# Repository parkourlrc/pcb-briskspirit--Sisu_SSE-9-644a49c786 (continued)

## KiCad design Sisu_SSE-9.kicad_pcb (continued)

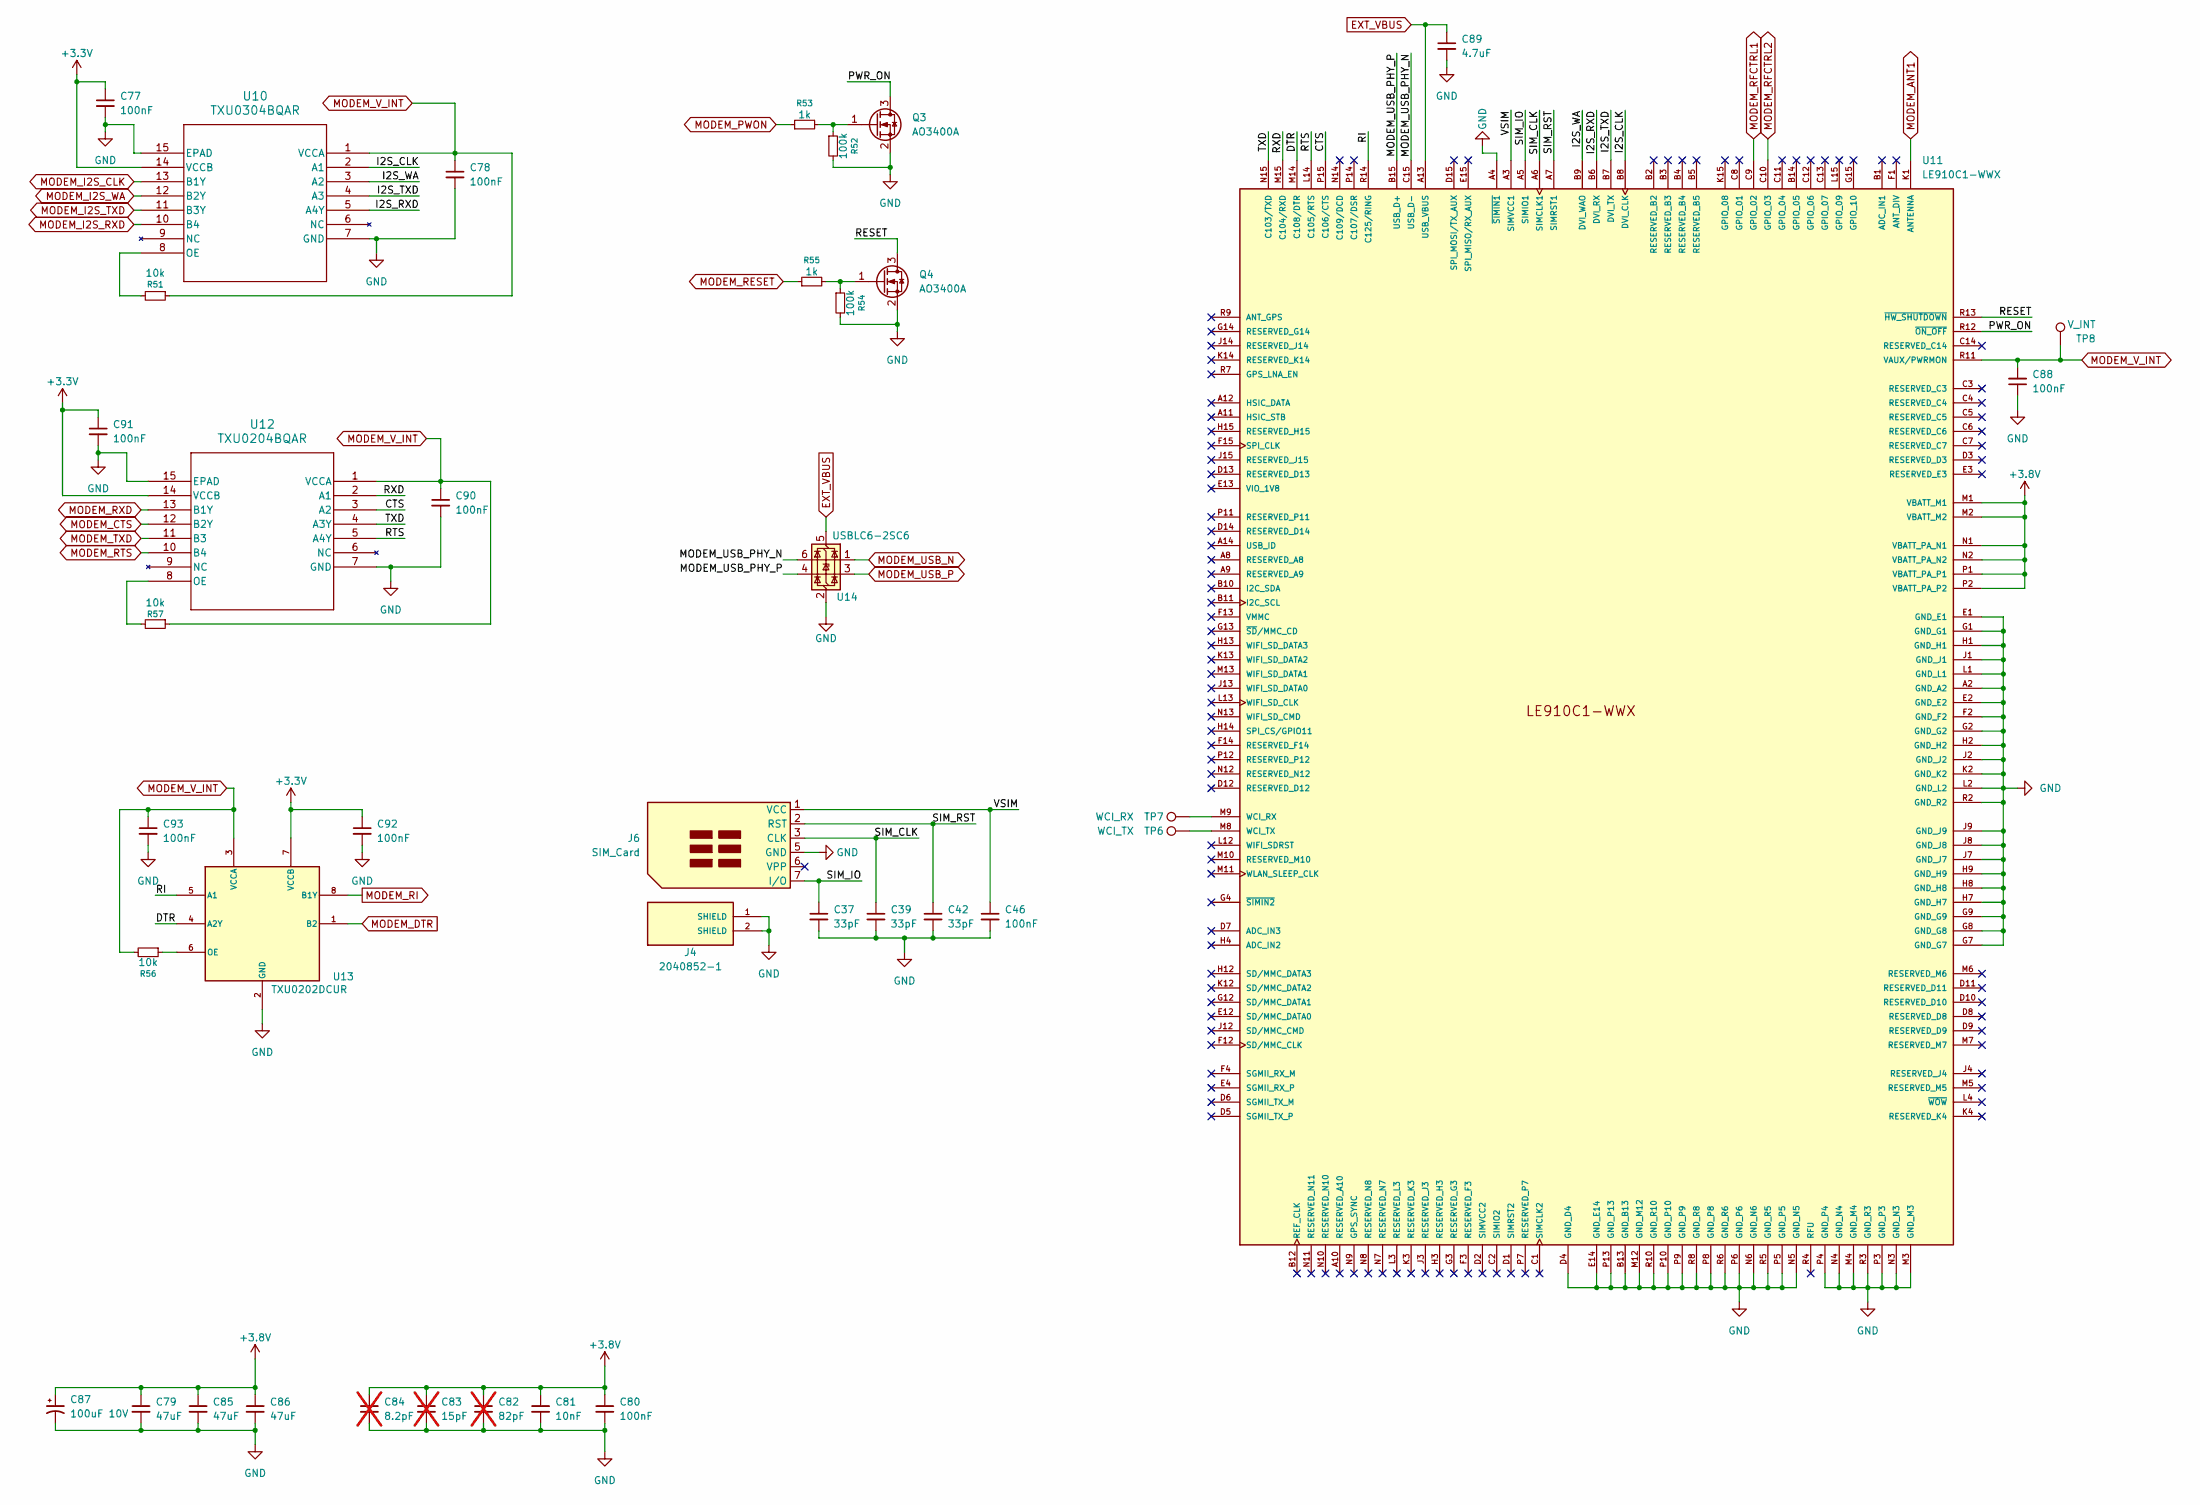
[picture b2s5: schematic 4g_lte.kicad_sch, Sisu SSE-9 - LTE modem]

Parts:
C37, C39, C42: 33pF; C_0402_1005Metric
C46, C77, C78, C80, C88, C90, C91, C92, C93: 100nF; C_0402_1005Metric
C79, C85, C86: 47uF; C_0805_2012Metric
C81: 10nF; C_0402_1005Metric
C82: 82pF; C_0402_1005Metric; not fitted
C83: 15pF; C_0402_1005Metric; not fitted
C84: 8.2pF; C_0402_1005Metric; not fitted
C87: 100uF 10V; CP_EIA-3528-21_Kemet-B
C89: 4.7uF; C_0603_1608Metric
J4: 2040852-1; TE_2040852-1; PARTREV A1
J6: SIM_Card; SIMslot_MUP_C7026-21
Q3, Q4: AO3400A; SOT-23
R51, R56, R57: 10k; R_0402_1005Metric
R52, R54: 100k; R_0402_1005Metric
R53, R55: 1k; R_0402_1005Metric
TP6: WCI_TX; TestPoint_Pad_D1.0mm
TP7: WCI_RX; TestPoint_Pad_D1.0mm
TP8: V_INT; TestPoint_Pad_D1.0mm
U10: TXU0304BQAR; DHWQFN-14-1EP_2.5x3mm_P0.5mm_EP1x1.5mm
U11: LE910C1-WWX; Telit_LE910C1-WWX_LGA-181_29.4x29.4mm; PARTREV 34
U12: TXU0204BQAR; DHWQFN-14-1EP_2.5x3mm_P0.5mm_EP1x1.5mm
U13: TXU0202DCUR; Texas_DCU0008A_VSSOP-8_2.3x2mm_P0.5mm
U14: USBLC6-2SC6; SOT-23-6

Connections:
+3.3V: C77.1, C91.1, C92.1, U10.14 (VCCB), U12.14 (VCCB), U13.7 (VCCB); also elsewhere on the board
+3.8V: C79.1, C80.1, C81.1, C82.1, C83.1, C84.1, C85.1, C86.1, C87.1, U11.M1 (VBATT_M1), U11.M2 (VBATT_M2), U11.N1 (VBATT_PA_N1), U11.N2 (VBATT_PA_N2), U11.P1 (VBATT_PA_P1), U11.P2 (VBATT_PA_P2); also elsewhere on the board
/4G LTE/CTS: U11.P15 (C106/CTS), U12.3 (A2)
/4G LTE/DTR: U11.M14 (C108/DTR), U13.4 (A2Y)
/4G LTE/I2S_CLK: U10.2 (A1), U11.B8 (DVI_CLK)
/4G LTE/I2S_RXD: U10.5 (A4Y), U11.B6 (DVI_RX)
/4G LTE/I2S_TXD: U10.4 (A3), U11.B7 (DVI_TX)
/4G LTE/I2S_WA: U10.3 (A2), U11.B9 (DVI_WAO)
/4G LTE/MODEM_USB_PHY_N: U11.C15 (USB_D-), U14.6 (I/O1)
/4G LTE/MODEM_USB_PHY_P: U11.B15 (USB_D+), U14.4 (I/O2)
/4G LTE/PWR_ON: Q3.3 (D), U11.R12 (~ON_OFF)
/4G LTE/RESET: Q4.3 (D), U11.R13 (~HW_SHUTDOWN)
/4G LTE/RI: U11.R14 (C125/RING), U13.5 (A1)
/4G LTE/RTS: U11.L14 (C105/RTS), U12.5 (A4Y)
/4G LTE/RXD: U11.M15 (C104/RXD), U12.2 (A1)
/4G LTE/SIM_CLK: C39.1, J6.3 (CLK), U11.A6 (SIMCLK1)
/4G LTE/SIM_IO: C37.1, J6.7 (I/O), U11.A5 (SIMIO1)
/4G LTE/SIM_RST: C42.1, J6.2 (RST), U11.A7 (SIMRST1)
/4G LTE/TXD: U11.N15 (C103/TXD), U12.4 (A3Y)
/4G LTE/VSIM: C46.1, J6.1 (VCC), U11.A3 (SIMVCC1)
EXT_VBUS: C89.1, U11.A13 (USB_VBUS), U14.5 (VBUS); also elsewhere on the board
GND: C37.2, C39.2, C42.2, C46.2, C77.2, C78.2, C79.2, C80.2, C81.2, C82.2, C83.2, C84.2, C85.2, C86.2, C87.2, C88.1, C89.2, C90.2, C91.2, C92.2, C93.2, J4.1 (SHIELD), J4.2 (SHIELD), J6.5 (GND), Q3.2 (S), Q4.2 (S), R52.2, R54.2, U10.7 (GND), U10.15 (EPAD), U11.A2 (GND_A2), U11.A4 (~SIMIN1), U11.B13 (GND_B13), U11.D4 (GND_D4), U11.E1 (GND_E1), U11.E2 (GND_E2), U11.E14 (GND_E14), U11.F2 (GND_F2), U11.G1 (GND_G1), U11.G2 (GND_G2), U11.G7 (GND_G7), U11.G8 (GND_G8), U11.G9 (GND_G9), U11.H1 (GND_H1), U11.H2 (GND_H2), U11.H7 (GND_H7), U11.H8 (GND_H8), U11.H9 (GND_H9), U11.J1 (GND_J1), U11.J2 (GND_J2), U11.J7 (GND_J7), U11.J8 (GND_J8), U11.J9 (GND_J9), U11.K2 (GND_K2), U11.L1 (GND_L1), U11.L2 (GND_L2), U11.M3 (GND_M3), U11.M4 (GND_M4), U11.M12 (GND_M12), U11.N3 (GND_N3), U11.N4 (GND_N4), U11.N5 (GND_N5), U11.N6 (GND_N6), U11.P3 (GND_P3), U11.P4 (GND_P4), U11.P5 (GND_P5), U11.P6 (GND_P6), U11.P8 (GND_P8), U11.P9 (GND_P9), U11.P10 (GND_P10), U11.P13 (GND_P13), U11.R2 (GND_R2), U11.R3 (GND_R3), U11.R5 (GND_R5), U11.R6 (GND_R6), U11.R8 (GND_R8), U11.R10 (GND_R10), U12.7 (GND), U12.15 (EPAD), U13.2 (GND), U14.2 (GND); also elsewhere on the board
MODEM_ANT1: U11.K1 (ANTENNA); also elsewhere on the board
MODEM_CTS: U12.12 (B2Y); also elsewhere on the board
MODEM_DTR: U13.1 (B2); also elsewhere on the board
MODEM_I2S_CLK: U10.13 (B1Y); also elsewhere on the board
MODEM_I2S_RXD: U10.10 (B4); also elsewhere on the board
MODEM_I2S_TXD: U10.11 (B3Y); also elsewhere on the board
MODEM_I2S_WA: U10.12 (B2Y); also elsewhere on the board
MODEM_PWON: R53.1; also elsewhere on the board
MODEM_RESET: R55.1; also elsewhere on the board
MODEM_RFCTRL1: U11.C9 (GPIO_02); also elsewhere on the board
MODEM_RFCTRL2: U11.C10 (GPIO_03); also elsewhere on the board
MODEM_RI: U13.8 (B1Y); also elsewhere on the board
MODEM_RTS: U12.10 (B4); also elsewhere on the board
MODEM_RXD: U12.13 (B1Y); also elsewhere on the board
MODEM_TXD: U12.11 (B3); also elsewhere on the board
MODEM_USB_N: U14.1 (I/O1); also elsewhere on the board
MODEM_USB_P: U14.3 (I/O2); also elsewhere on the board
MODEM_V_INT: C78.1, C88.2, C90.1, C93.1, R51.1, R56.2, R57.1, TP8.1 (1_1), U10.1 (VCCA), U11.R11 (VAUX/PWRMON), U12.1 (VCCA), U13.3 (VCCA); also elsewhere on the board
unnamed: Q3.1 (G), R52.1, R53.2
unnamed: Q4.1 (G), R54.1, R55.2
unnamed: R51.2, U10.8 (OE)
unnamed: TP7.1 (1_1), U11.M9 (WCI_RX)
unnamed: TP6.1 (1_1), U11.M8 (WCI_TX)
unnamed: R57.2, U12.8 (OE)
unnamed: R56.1, U13.6 (OE)

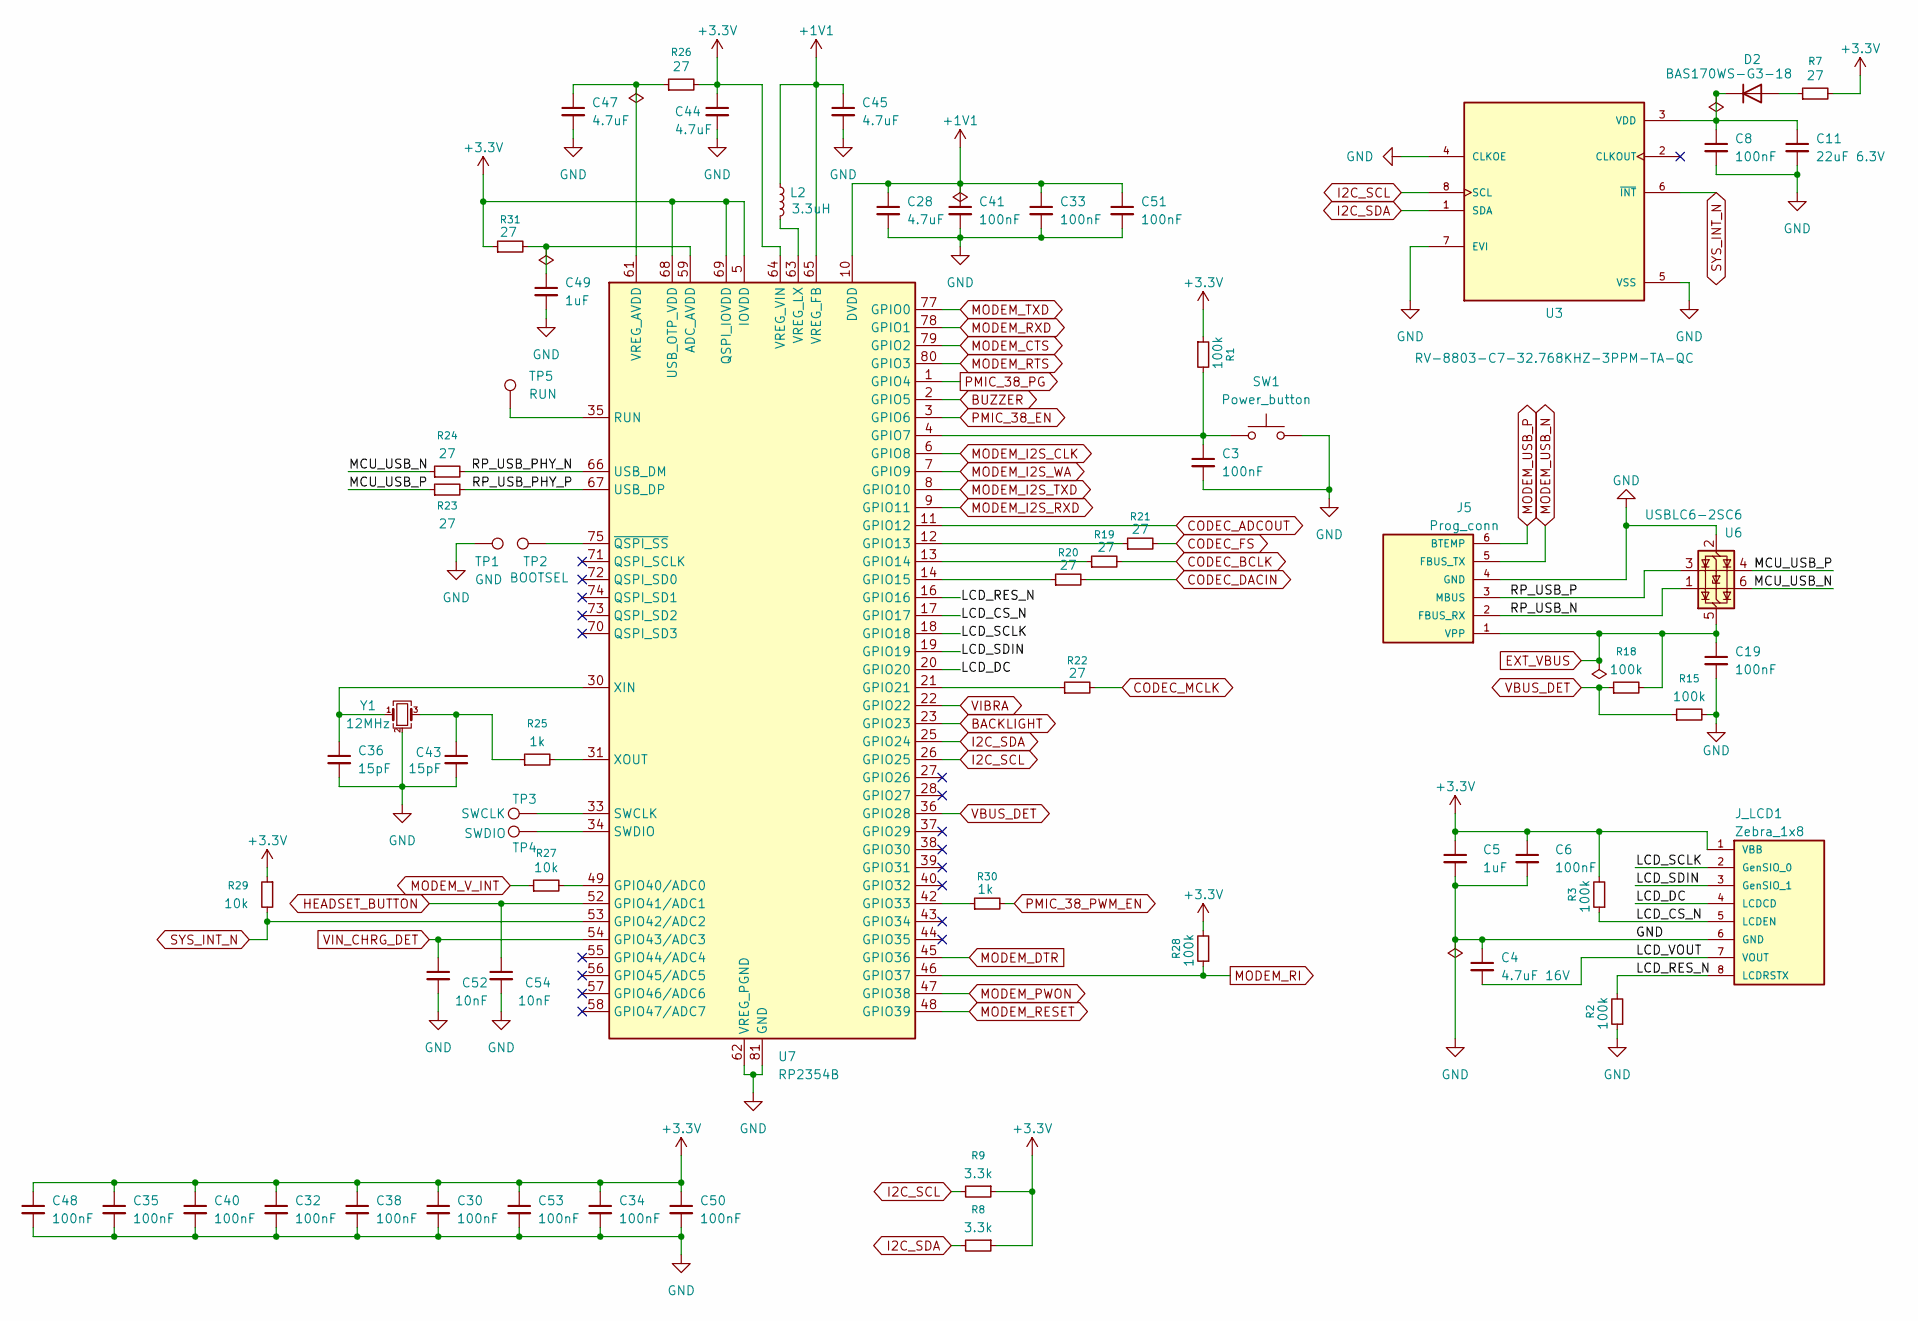
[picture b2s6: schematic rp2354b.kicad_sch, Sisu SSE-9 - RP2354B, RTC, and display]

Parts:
C3, C6, C8, C19, C30, C32, C33, C34, C35, C38, C40, C41, C48, C50, C51, C53: 100nF; C_0402_1005Metric
C4: 4.7uF 16V; C_0603_1608Metric
C5, C49: 1uF; C_0402_1005Metric
C11: 22uF 6.3V; C_0603_1608Metric
C28, C44, C45, C47: 4.7uF; C_0603_1608Metric
C36, C43: 15pF; C_0402_1005Metric
C52, C54: 10nF; C_0402_1005Metric
D2: BAS170WS-G3-18; D_SOD-323
J5: Prog_conn; 3210_prog_connector
J_LCD1: Zebra_1x8; 3210_display_zebra
L2: 3.3uH; L_Changjiang_FTC201610S; MPN AOTA-B201610S3R3-101-T
R1, R2, R3, R15, R18, R28: 100k; R_0402_1005Metric
R7, R19, R20, R21, R22, R23, R24, R26, R31: 27; R_0402_1005Metric
R8, R9: 3.3k; R_0402_1005Metric
R25, R30: 1k; R_0402_1005Metric
R27, R29: 10k; R_0402_1005Metric
SW1: Power_button; Panasonic_EVQPUJ_EVQPUA
TP1: GND; TestPoint_Pad_D1.0mm
TP2: BOOTSEL; TestPoint_Pad_D1.0mm
TP3: SWCLK; TestPoint_Pad_D1.0mm
TP4: SWDIO; TestPoint_Pad_D1.0mm
TP5: RUN; TestPoint_Pad_D1.0mm
U3: RV-8803-C7-32.768KHZ-3PPM-TA-QC; IC_RV-8803-C7-32.768KHZ-3PPM-TA-QC; PARTREV 5.1/06.2018
U6: USBLC6-2SC6; SOT-23-6
U7: RP2354B; RP2354B_QFN-80-1EP_10x10mm_P0.4mm_EP3.4x3.4mm
Y1: 12MHz; Crystal_SMD_3225-4Pin_3.2x2.5mm

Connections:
+1V1: C28.1, C33.1, C41.1, C45.1, C51.1, L2.1, U7.10 (DVDD), U7.32 (DVDD), U7.51 (DVDD), U7.65 (VREG_FB)
+3.3V: C5.1, C6.1, C30.1, C32.1, C34.1, C35.1, C38.1, C40.1, C44.1, C48.1, C50.1, C53.1, J_LCD1.1 (VBB), R1.1, R3.2, R7.2, R8.1, R9.1, R26.2, R28.2, R29.1, R31.1, U7.5 (IOVDD), U7.15 (IOVDD), U7.24 (IOVDD), U7.29 (IOVDD), U7.41 (IOVDD), U7.50 (IOVDD), U7.60 (IOVDD), U7.64 (VREG_VIN), U7.68 (USB_OTP_VDD), U7.69 (QSPI_IOVDD), U7.76 (IOVDD); also elsewhere on the board
/RP2354B / RTC / DISPLAY/LCD_CS_N: J_LCD1.5 (LCDEN), R3.1, U7.17 (GPIO17)
/RP2354B / RTC / DISPLAY/LCD_DC: J_LCD1.4 (LCDCD), U7.20 (GPIO20)
/RP2354B / RTC / DISPLAY/LCD_RES_N: J_LCD1.8 (LCDRSTX), R2.2, U7.16 (GPIO16)
/RP2354B / RTC / DISPLAY/LCD_SCLK: J_LCD1.2 (GenSIO_0), U7.18 (GPIO18)
/RP2354B / RTC / DISPLAY/LCD_SDIN: J_LCD1.3 (GenSIO_1), U7.19 (GPIO19)
/RP2354B / RTC / DISPLAY/LCD_VOUT: C4.2, J_LCD1.7 (VOUT)
/RP2354B / RTC / DISPLAY/MCU_USB_N: R24.1, U6.6 (I/O1)
/RP2354B / RTC / DISPLAY/MCU_USB_P: R23.1, U6.4 (I/O2)
/RP2354B / RTC / DISPLAY/RP_USB_N: J5.2 (FBUS_RX), U6.1 (I/O1)
/RP2354B / RTC / DISPLAY/RP_USB_P: J5.3 (MBUS), U6.3 (I/O2)
/RP2354B / RTC / DISPLAY/RP_USB_PHY_N: R24.2, U7.66 (USB_DM)
/RP2354B / RTC / DISPLAY/RP_USB_PHY_P: R23.2, U7.67 (USB_DP)
BACKLIGHT: U7.23 (GPIO23); also elsewhere on the board
BUZZER: U7.2 (GPIO5); also elsewhere on the board
CODEC_ADCOUT: U7.11 (GPIO12); also elsewhere on the board
CODEC_BCLK: R19.2; also elsewhere on the board
CODEC_DACIN: R20.2; also elsewhere on the board
CODEC_FS: R21.2; also elsewhere on the board
CODEC_MCLK: R22.2; also elsewhere on the board
EXT_VBUS: C19.1, J5.1 (VPP), R18.2, U6.5 (VBUS); also elsewhere on the board
GND: C3.2, C4.1, C5.2, C6.2, C8.2, C11.2, C19.2, C28.2, C30.2, C32.2, C33.2, C34.2, C35.2, C36.2, C38.2, C40.2, C41.2, C43.2, C44.2, C45.2, C47.2, C48.2, C49.2, C50.2, C51.2, C52.2, C53.2, C54.2, J5.4 (GND), J_LCD1.6 (GND), R2.1, R15.2, SW1.2, TP1.1 (1_1), U3.4 (CLKOE), U3.5 (VSS), U3.7 (EVI), U6.2 (GND), U7.62 (VREG_PGND), U7.81 (GND), Y1.2 (G), Y1.4 (G); also elsewhere on the board
HEADSET_BUTTON: C54.1, U7.52 (GPIO41/ADC1); also elsewhere on the board
I2C_SCL: R9.2, U3.8 (SCL), U7.26 (GPIO25); also elsewhere on the board
I2C_SDA: R8.2, U3.1 (SDA), U7.25 (GPIO24); also elsewhere on the board
MODEM_CTS: U7.79 (GPIO2); also elsewhere on the board
MODEM_DTR: U7.45 (GPIO36); also elsewhere on the board
MODEM_I2S_CLK: U7.6 (GPIO8); also elsewhere on the board
MODEM_I2S_RXD: U7.9 (GPIO11); also elsewhere on the board
MODEM_I2S_TXD: U7.8 (GPIO10); also elsewhere on the board
MODEM_I2S_WA: U7.7 (GPIO9); also elsewhere on the board
MODEM_PWON: U7.47 (GPIO38); also elsewhere on the board
MODEM_RESET: U7.48 (GPIO39); also elsewhere on the board
MODEM_RI: R28.1, U7.46 (GPIO37); also elsewhere on the board
MODEM_RTS: U7.80 (GPIO3); also elsewhere on the board
MODEM_RXD: U7.78 (GPIO1); also elsewhere on the board
MODEM_TXD: U7.77 (GPIO0); also elsewhere on the board
MODEM_USB_N: J5.5 (FBUS_TX); also elsewhere on the board
MODEM_USB_P: J5.6 (BTEMP); also elsewhere on the board
MODEM_V_INT: R27.1; also elsewhere on the board
unnamed: C43.1, R25.1, Y1.3
unnamed: D2.2 (A), R7.1
unnamed: C8.1, C11.1, D2.1 (K), U3.3 (VDD)
unnamed: C49.1, R31.2, U7.59 (ADC_AVDD)
unnamed: C3.1, R1.2, SW1.1, U7.4 (GPIO7)
unnamed: R21.1, U7.12 (GPIO13)
unnamed: R19.1, U7.13 (GPIO14)
unnamed: R20.1, U7.14 (GPIO15)
unnamed: R22.1, U7.21 (GPIO21)
unnamed: R30.1, U7.42 (GPIO33)
unnamed: R27.2, U7.49 (GPIO40/ADC0)
unnamed: TP5.1 (1_1), U7.35 (RUN)
unnamed: TP3.1 (1_1), U7.33 (SWCLK)
unnamed: TP4.1 (1_1), U7.34 (SWDIO)
unnamed: C47.1, R26.1, U7.61 (VREG_AVDD)
unnamed: L2.2, U7.63 (VREG_LX)
unnamed: C36.1, U7.30 (XIN), Y1.1
unnamed: R25.2, U7.31 (XOUT)
unnamed: TP2.1 (1_1), U7.75 (~QSPI_SS)
PMIC_38_EN: U7.3 (GPIO6); also elsewhere on the board
PMIC_38_PG: U7.1 (GPIO4); also elsewhere on the board
PMIC_38_PWM_EN: R30.2; also elsewhere on the board
SYS_INT_N: R29.2, U3.6 (~INT), U7.53 (GPIO42/ADC2); also elsewhere on the board
VBUS_DET: R15.1, R18.1, U7.36 (GPIO28)
VIBRA: U7.22 (GPIO22); also elsewhere on the board
VIN_CHRG_DET: C52.1, U7.54 (GPIO43/ADC3); also elsewhere on the board

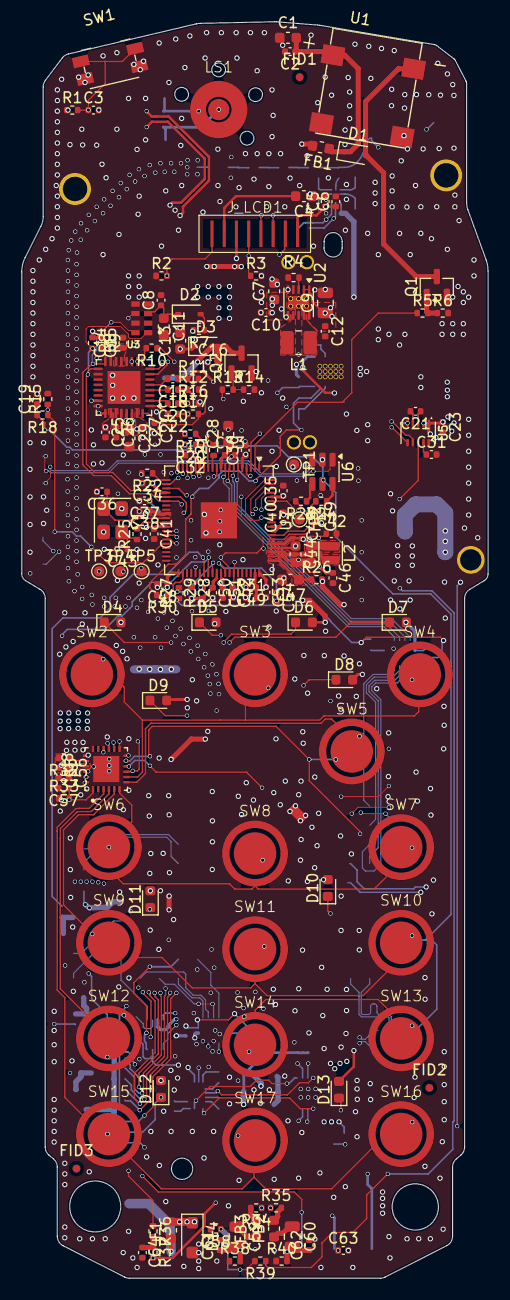
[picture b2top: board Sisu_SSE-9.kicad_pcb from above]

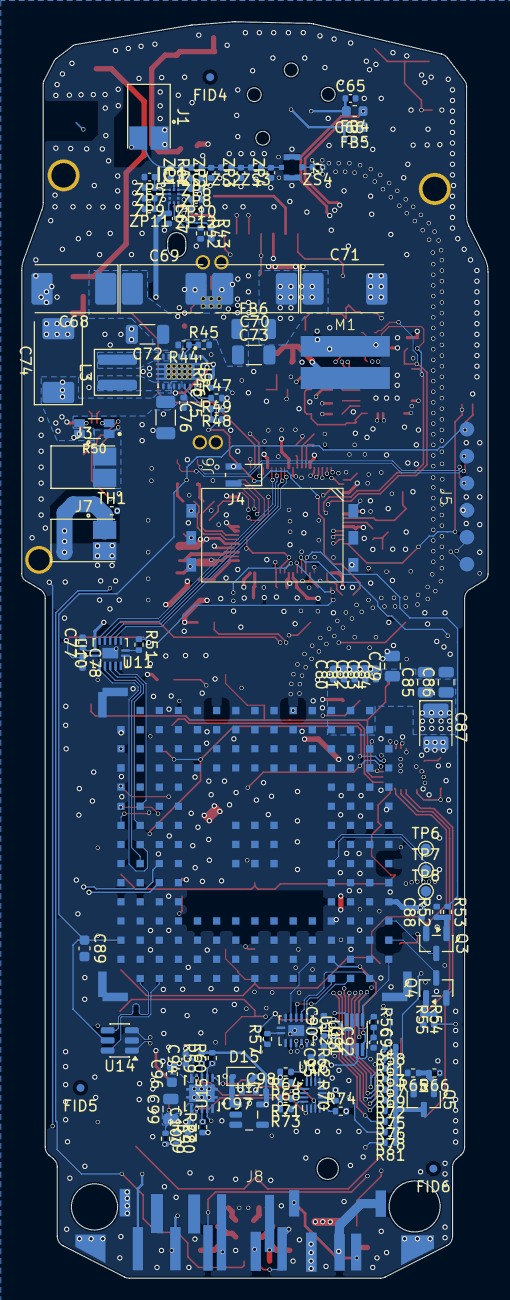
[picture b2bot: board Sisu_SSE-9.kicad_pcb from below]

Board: 6 copper layers, 43.9 x 118.2 mm, 296 parts (127 on the bottom side), 192 nets.

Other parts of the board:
FID1, FID2, FID3, FID4, FID5, FID6: Fiducial_0.75mm_Mask1.5mm
H1, H2: PTH_GND_Hole_2.30mm
H3, H4, H5, H6: PTH_GND_Hole_0.95mm
H7: PTH_GND_Hole_2.00mm

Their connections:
GND: H1.1 (GND), H2.1 (GND), H3.1 (GND), H4.1 (GND), H5.1 (GND), H6.1 (GND), H7.1 (GND); also elsewhere on the board

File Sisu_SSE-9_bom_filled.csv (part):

"Id";"Designator";"Footprint";"Quantity";"Designation";"Supplier and ref";"MPN Source/Reason";"Digi-Key PN";"Preferred Supplier";"Digi-Key/Product URL";"Stock Check";"Footprint Check";"Value/Voltage Check";"Assembly/Review Notes"
"1";"C1, C7, C11, C29, C96";"C_0603_1608Metric";"5";"22uF 6.3V";"GRM188R60J226MEA0J";"current schematic Datasheet/MPN; prior supplier metadata retained";"490-GRM188R60J226MEA0JCT-ND";"Digi-Key";"https://www.digikey.com/en/products/detail/murata-electronic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";"Digi-Key search showed in stock; verify at order time.";"OK: 0603 MLCC.";"OK: 22uF 6.3V. | Selected 22uF 6.3V; verify if rail can exceed 6.3V.";""
"2";"C2, C3, C6, C8, C10, C12, C14, C15, C16, C19, C23, C25, C27, C30, C32, C33, C34, C35, C38, C40, C41, C46, C48, C50, C51, C53, C56, C67, C75, C77, C78, C80, C88, C90, C91, C92, C93, C95, C97, C100";"C_0402_1005Metric";"40";"100nF";"GCM155R71H104KE02J";"current schematic Datasheet/MPN; prior supplier metadata retained";"";"Digi-Key";"https://www.digikey.com/en/products/detail/murata-electronic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";"Digi-Key search showed high stock; verify at order time.";"OK: 0402 MLCC.";"OK: 100nF; 50V X7R family.";""
"3";"C4";"C_0603_1608Metric";"1";"4.7uF 16V";"CL10A475KO8NNNC";"current schematic Datasheet/MPN; prior supplier metadata retained";"";"Digi-Key";"https://www.digikey.com/en/products/detail/samsung-electro-m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";"Digi-Key search showed in stock; verify at order time.";"OK: 0603 MLCC. | OK after replacement: selected MPN is 0603.";"OK: 4.7uF 16V. | OK: 4.7uF; selected 16V part.";""
"4";"C5, C17, C18, C20, C22, C24, C31, C49, C94, C98";"C_0402_1005Metric";"10";"1uF";"CL05A105KO5NNNC";"current schematic Datasheet/MPN; prior supplier metadata retained";"";"Digi-Key";"https://www.digikey.com/en/products/detail/samsung-electro-m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";"Digi-Key search showed high stock; verify at order time.";"OK: 0402 MLCC.";"OK: 1uF; 16V X5R/X7R-class MLCC.";"C98 specifically should be retrofitted from 1uF to 4.7uF for TPS7B69 stability; see ERRATA.md."
"5";"C9";"C_0805_2012Metric";"1";"22uF 10V";"GRM21BR61A226ME51L";"current schematic Datasheet/MPN; prior supplier metadata retained";"";"Digi-Key";"https://www.digikey.com/en/products/detail/murata-electronic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";"Verify at order time.";"OK: 0805 MLCC.";"OK: 22uF 10V.";""
"6";"C13";"C_0603_1608Metric";"1";"22uF";"GRM188R60J226MEA0J";"current schematic Datasheet/MPN; prior supplier metadata retained";"490-GRM188R60J226MEA0JCT-ND";"Digi-Key";"https://www.digikey.com/en/products/detail/murata-electronic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";"Digi-Key search showed in stock; verify at order time.";"OK: 0603 MLCC.";"OK: 22uF 6.3V. | Selected 22uF 6.3V; verify if rail can exceed 6.3V.";""
"7";"C21";"C_0402_1005Metric";"1";"470nF";"GRM155R61A474KE15D";"current schematic Datasheet/MPN; prior supplier metadata retained";"";"";"";"Not rechecked for revB2.";"Current KiCad footprint: C_0402_1005Metric; supplier land pattern not rechecked in this update.";"Current schematic value(s): 470nF; reverify against MPN before ordering.";""
"8";"C26, C55";"C_0402_1005Metric";"2";"4.7uF";"CL05A475MP5NRNC";"current schematic Datasheet/MPN; prior supplier metadata retained";"";"Digi-Key";"https://www.digikey.com/en/products/detail/samsung-electro-m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";"Digi-Key search showed high stock; verify at order time.";"OK: 0402 MLCC.";"OK: 4.7uF; 10V-class MLCC.";""
"9";"C28, C44, C45, C47, C89";"C_0603_1608Metric";"5";"4.7uF";"CL10A475KO8NNNC";"current schematic Datasheet/MPN; prior supplier metadata retained";"";"Digi-Key";"https://www.digikey.com/en/products/detail/samsung-electro-m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";"Digi-Key search showed in stock; verify at order time.";"OK: 0603 MLCC. | OK after replacement: selected MPN is 0603.";"OK: 4.7uF 16V. | OK: 4.7uF; selected 16V part.";""
"10";"C36, C43";"C_0402_1005Metric";"2";"15pF";"GJM1555C1H150FB01D";"current schematic Datasheet/MPN; prior supplier metadata retained";"";"Digi-Key";"https://www.digikey.com/en/products/filter/ceramic-capacitor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";"Digi-Key filter showed 15pF 0402 C0G options in stock; verify exact MPN at order time.";"OK: 0402 C0G.";"OK: 15pF, 50V C0G/NP0; matches Raspberry Pi RP2350-family guidance for ABM8-272-T3 with expected board parasitics. | OK: 15pF, 50V C0G/NP0.";""
"11";"C37, C39, C42, C58, C61, C62, C63, C65, C66";"C_0402_1005Metric";"9";"33pF";"CL05C330JB5NNNC";"current schematic Datasheet/MPN; prior supplier metadata retained";"1276-1272-1-ND";"Digi-Key";"https://www.digikey.com/en/products/detail/samsung-electro-m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";"Digi-Key product page says ships today; verify at order time.";"OK: 0402 C0G.";"OK: 33pF, 50V C0G/NP0.";""
"12";"C52, C54, C57, C81";"C_0402_1005Metric";"4";"10nF";"GCM155R71H103KA55D";"current schematic Datasheet/MPN; prior supplier metadata retained";"490-4762-1-ND";"Digi-Key";"https://www.digikey.com/en/products/detail/murata-electronic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";"Digi-Key showed in stock; verify at order time.";"OK after replacement: selected 0402. Original GRM1885C1H103JA01D is 0603 and does not match PCB.";"OK: 10nF 50V, but selected dielectric is X7R. 10nF C0G generally was not available in 0402 from the in-stock Digi-Key search.";""
"13";"C59, C60";"C_0805_2012Metric";"2";"47uF 6.3V";"CL21A476MQYNNNG";"current schematic Datasheet/MPN; prior supplier metadata retained";"1276-6467-1-ND";"Digi-Key";"https://www.digikey.com/en/products/detail/samsung-electro-m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";"Digi-Key showed in stock; verify at order time.";"OK: 0805 MLCC.";"OK: 47uF 6.3V. | 47uF 6.3V; BOM did not list voltage, so verify no instance sees >6.3V.";""
"14";"C64";"C_0402_1005Metric";"1";"1nF";"GRM1555C1H102JA01D";"current schematic Datasheet/MPN; prior supplier metadata retained";"490-3244-1-ND";"Digi-Key";"https://www.digikey.com/en/products/detail/murata-electronic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";"Digi-Key showed in stock; verify at order time.";"OK: 0402 C0G.";"OK: 1nF, 50V C0G/NP0.";""
"15";"C68, C69, C70, C71, C74";"CP_EIA-7343-43_AVX-E_Reflow";"5";"470uF 10V";"TPSE477M010R0045";"current schematic Datasheet/MPN; prior supplier metadata retained";"478-4148-1-ND";"Digi-Key";"https://www.digikey.com/en/products/detail/kyocera-avx/TPSE4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";"Digi-Key search showed in stock; verify at order time.";"Current KiCad footprint: CP_EIA-7343-43_AVX-E_Reflow; supplier land pattern not rechecked in this update.";"OK: 470uF, 10V matches BOM.";""
"16";"C72, C73, C76";"C_1206_3216Metric";"3";"22uF 10V";"CL31A226MOCLNNC";"current schematic Datasheet/MPN; prior supplier metadata retained";"";"Digi-Key";"https://www.digikey.com/en/products/detail/samsung-electro-m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";"Verify at order time.";"OK: 1206 MLCC.";"OK: 22uF 10V.";""
"17";"C79, C85, C86";"C_0805_2012Metric";"3";"47uF";"CL21A476MQYNNNG";"current schematic Datasheet/MPN; prior supplier metadata retained";"1276-6467-1-ND";"Digi-Key";"https://www.digikey.com/en/products/detail/samsung-electro-m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";"Digi-Key showed in stock; verify at order time.";"OK: 0805 MLCC.";"OK: 47uF 6.3V. | 47uF 6.3V; BOM did not list voltage, so verify no instance sees >6.3V.";""
"18";"C82";"C_0402_1005Metric";"1";"82pF";"GRM1555C1H820JA01D";"DNP in current schematic; no order required";"";"DNP / no order";"";"DNP / no order.";"Current KiCad footprint: C_0402_1005Metric.";"DNP in current schematic.";"Optional modem-supply RF shunt capacitor; prior nominal 82pF; leave unpopulated."
"19";"C83";"C_0402_1005Metric";"1";"15pF";"GJM1555C1H150FB01D";"DNP in current schematic; no order required";"";"DNP / no order";"";"DNP / no order.";"Current KiCad footprint: C_0402_1005Metric.";"DNP in current schematic.";"Optional modem-supply RF shunt capacitor; prior nominal 15pF; leave unpopulated."
"20";"C84";"C_0402_1005Metric";"1";"8.2pF";"GJM1555C1H8R2CB01D";"DNP in current schematic; no order required";"";"DNP / no order";"";"DNP / no order.";"Current KiCad footprint: C_0402_1005Metric.";"DNP in current schematic.";"Optional modem-supply RF shunt capacitor; prior nominal 82pF; leave unpopulated."
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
